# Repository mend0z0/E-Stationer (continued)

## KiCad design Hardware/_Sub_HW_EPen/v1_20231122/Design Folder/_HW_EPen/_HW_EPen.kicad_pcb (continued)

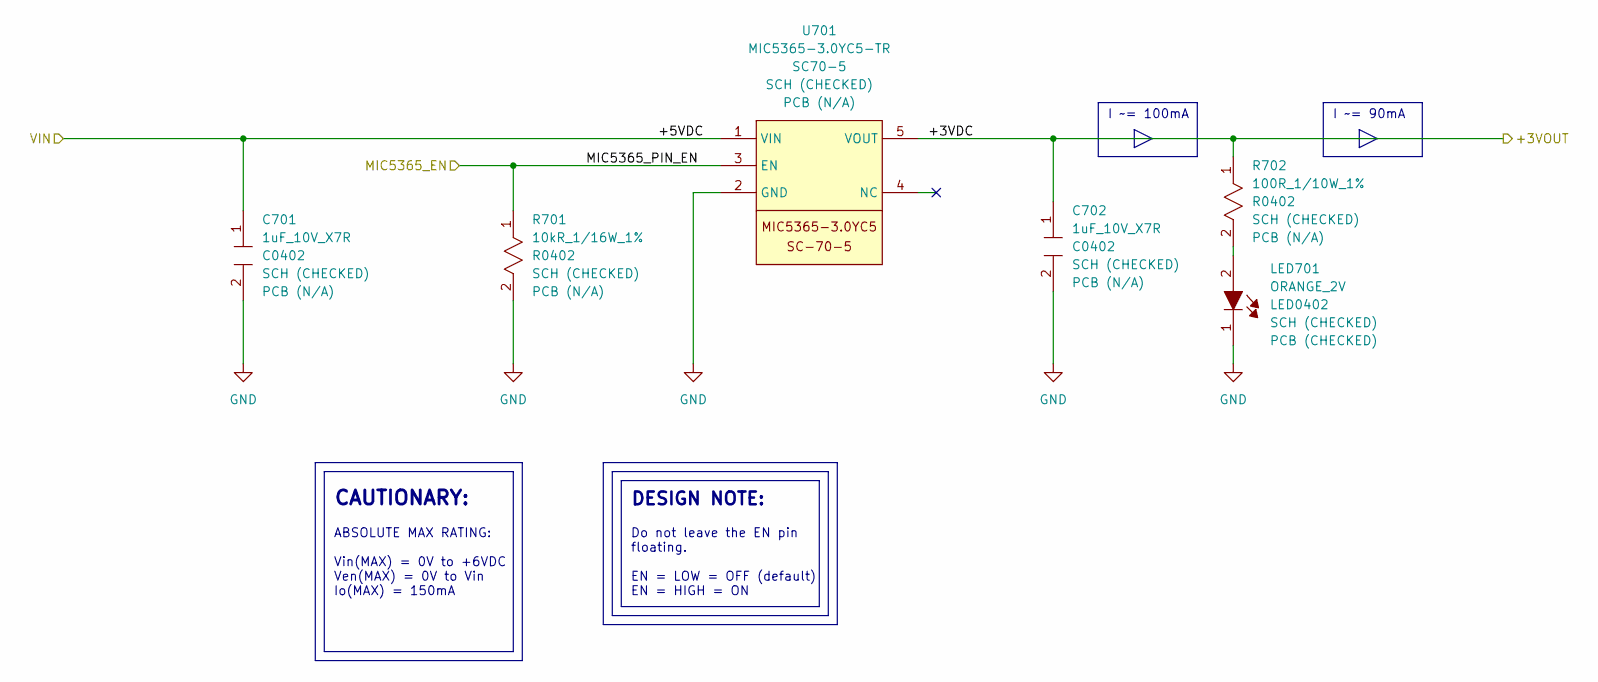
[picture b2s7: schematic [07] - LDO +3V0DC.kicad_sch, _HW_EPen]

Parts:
C701, C702: 1uF_10V_X7R; C_0402_1005Metric; Part Number (Vendor) 490-GRM155Z71A105KE01DTR-ND
LED701: ORANGE_2V; LED_0402_1005Metric; Part Number (Vendor) 3147-B2841UD--20D000614U1930TR-ND
R701: 10kR_1/16W_1%; R_0402_1005Metric; Part Number (Vendor) CR0402-FX-1002GLFTR-ND
R702: 100R_1/10W_1%; R_0402_1005Metric; Part Number (Vendor) 2019-RK73H1ETTP1000FTR-ND
U701: MIC5365-3.0YC5-TR; SOT-353_SC-70-5; Part Number (Vendor) 576-3191-2-ND

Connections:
/BLOCK DIAGRAM/LDO +3V0DC/+3VDC: C702.1, R702.1, U701.5 (VOUT); also elsewhere on the board
/BLOCK DIAGRAM/LDO +3V0DC/+5VDC: C701.1, U701.1 (VIN); also elsewhere on the board
/BLOCK DIAGRAM/LDO +3V0DC/MIC5365_PIN_EN: R701.1, U701.3 (EN); also elsewhere on the board
GND: C701.2, C702.2, LED701.1, R701.2, U701.2 (GND); also elsewhere on the board
unnamed: LED701.2, R702.2

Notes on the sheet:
CAUTIONARY:
I ~= 100mA
I ~= 90mA
Do not leave the EN pin floating. EN = LOW = OFF (default) EN = HIGH = ON
DESIGN NOTE:
ABSOLUTE MAX RATING: Vin(MAX) = 0V to +6VDC Ven(MAX) = 0V to Vin Io(MAX) = 150mA

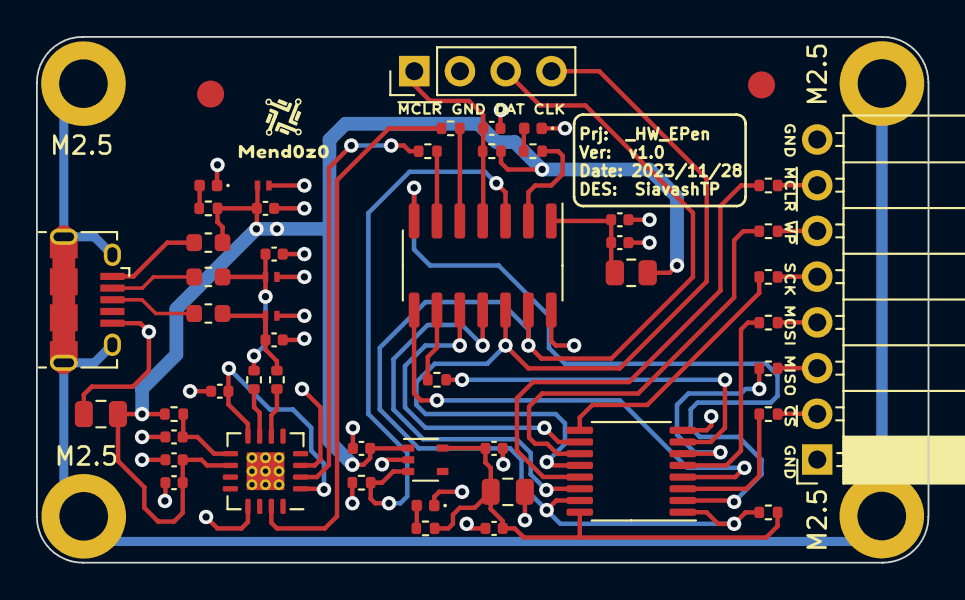
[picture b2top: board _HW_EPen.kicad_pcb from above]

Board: 2 copper layers, 49.5 x 29.2 mm, 57 parts (0 on the bottom side), 44 nets.

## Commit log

2023-11-20 Adding folder
2023-11-21 Uploading new files
2023-11-21 Adding Block diagrams
2023-11-21 Updating Block Diagrams
2023-11-21 Updateing README and Block Diagram
2023-11-22 Uploading HW Project file
2023-11-25 Working on EPen Schematic
2023-11-27 Updating the Hardware section
2023-11-27 Updating Readmes
2023-11-27 More progress on EPen Hardware
2023-11-28 _HW_EPen is ready to be worked for layout
2023-11-28 Working on PCB layout
2023-11-29 EPen layout is almost done
2023-11-29 Working on EPaper Schematic
2023-12-03 Working on E-Paper schematic
2023-12-04 EPaper schematic is almost done...
2023-12-16 Latest update
2023-12-16 Adding screenshot
2023-12-18 Working on epaper hardware
2023-12-18 Hardware is almost done
2023-12-19 Updating file templates and structures...
2023-12-20 Updating Hardware File structures
2023-12-21 Updating Symbol library naming
2023-12-25 some update
